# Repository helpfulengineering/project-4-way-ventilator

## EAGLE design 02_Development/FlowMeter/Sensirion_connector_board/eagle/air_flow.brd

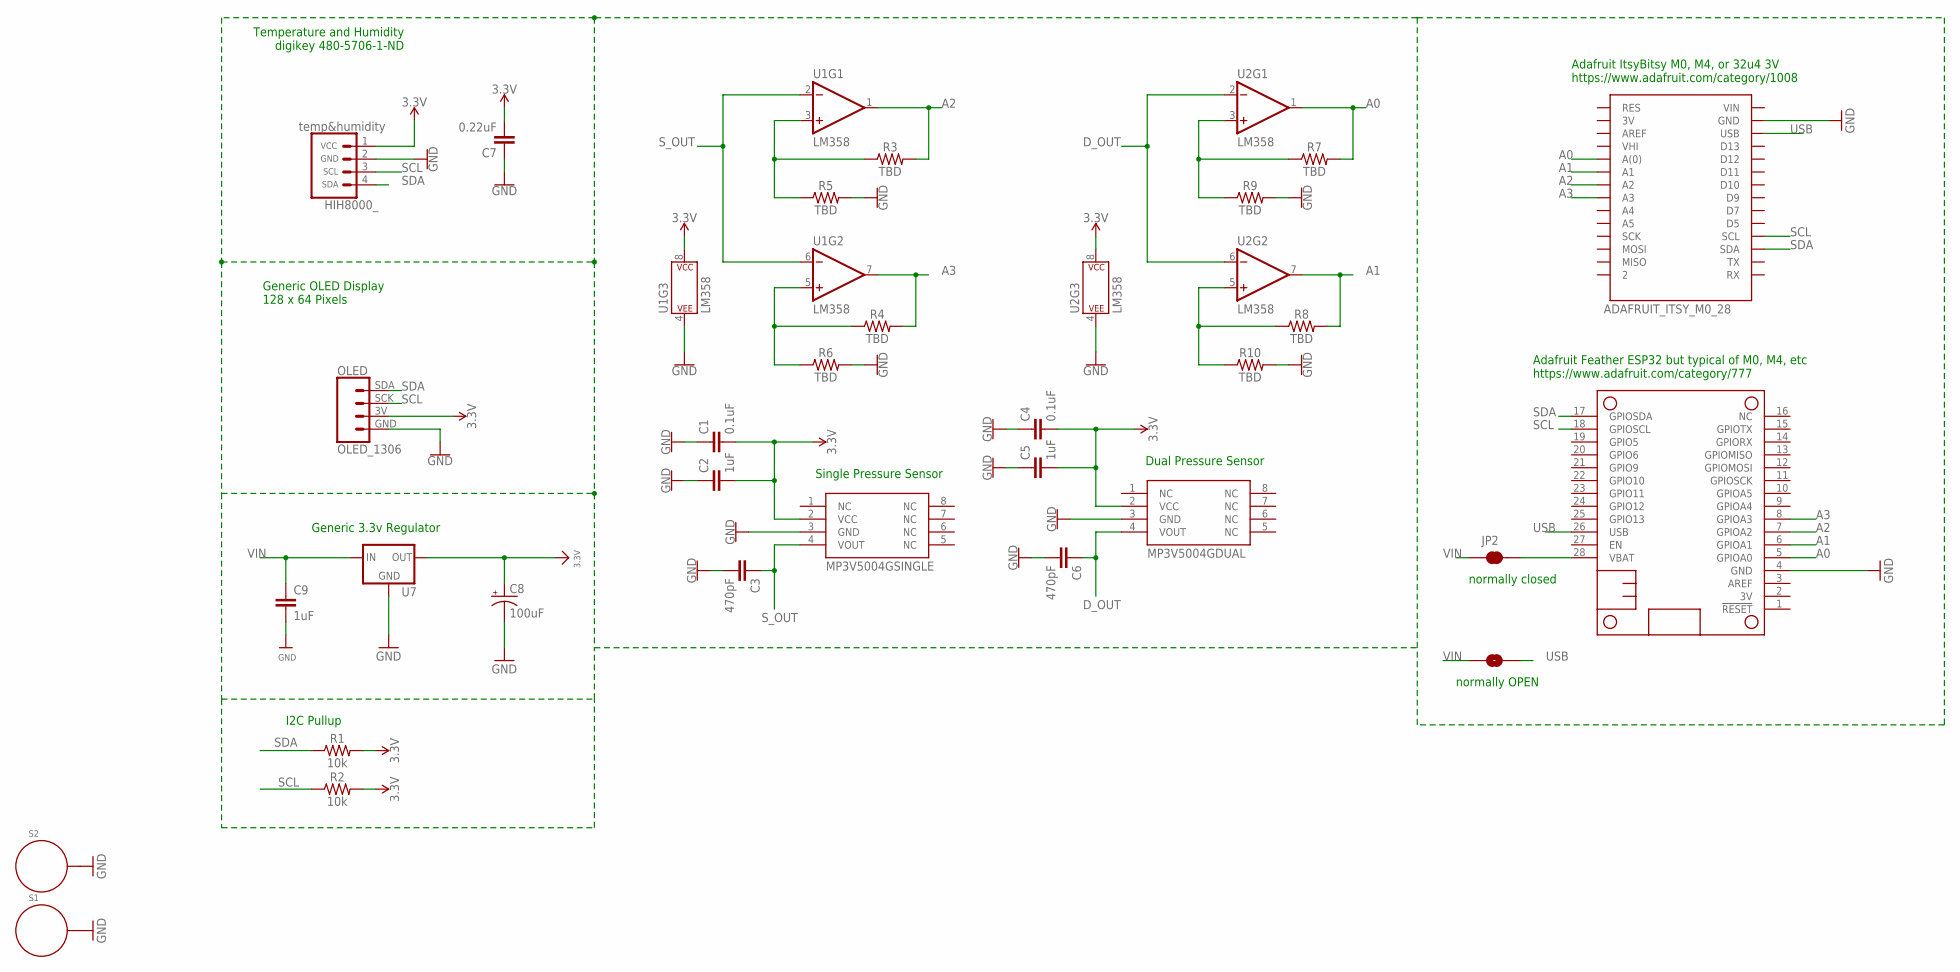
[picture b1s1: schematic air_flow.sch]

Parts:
C1, C4: 0.1uF; CAP-PTH-SMALL-KIT
C2, C5, C9: 1uF; CAP-PTH-SMALL-KIT
C3, C6: 470pF; CAP-PTH-SMALL-KIT
C7: 0.22uF; CAP-PTH-SMALL-KIT
C8: 100uF; E3,5-8
JP1: JUMPER-SMT_2_NO_NO-SILK; SMT-JUMPER_2_NO_NO-SILK
JP2: JUMPER-SMT_2_NC_TRACE_SILK; SMT-JUMPER_2_NC_TRACE_SILK
MS2: FEATHERWING_NODIM; FEATHERWING_DIM
R1, R2: 10k; AXIAL-0.3
R3, R4, R5, R6, R7, R8, R9, R10: TBD; AXIAL-0.3
S1, S2: STANDOFF_ELECTRICAL5-32; STANDOFF_ELECTRICAL_5_32
U1, U2: LM358; DIP08
U7: V_REG_78XXSINK; TO220-IGO
U$1: OLED_1306
U$2: MP3V5004GSINGLE; MP3V5004GP
U$3: MP3V5004GDUAL; MP3V5004DP
U$4: HIH8000_; HIH8120_TH
U$45: ADAFRUIT_ITSY_M0_28; ADAFRUIT_ITS_MO_28

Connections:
3.3V: C1.2, C2.2, C4.2, C5.2, C7.2, C8.+, R1.P$2 (2), R2.P$2 (2), U1.8 (P$V+), U2.8 (P$V+), U7.OUT, U$1.3V (VCC), U$2.2 (VCC), U$3.2 (VCC), U$4.1 (VCC)
A0: MS2.5 (GPIOA0), R7.P$2 (2), U2.1 (OUT), U$45.A0 (A(0))
A1: MS2.6 (GPIOA1), R8.P$2 (2), U2.7 (OUT), U$45.A1
A2: MS2.7 (GPIOA2), R3.P$2 (2), U1.1 (OUT), U$45.A2
A3: MS2.8 (GPIOA3), R4.P$2 (2), U1.7 (OUT), U$45.A3
D_OUT: C6.1, U2.2 (-IN), U2.6 (-IN), U$3.4 (VOUT)
GND: C1.1, C2.1, C3.2, C4.1, C5.1, C6.2, C7.1, C8.-, C9.2, MS2.4 (GND), R5.P$2 (2), R6.P$2 (2), R9.P$2 (2), R10.P$2 (2), S1.P1, S2.P1, U1.4 (P$V-), U2.4 (P$V-), U7.GND, U$1.GND, U$2.3 (GND), U$3.3 (GND), U$4.2 (GND), U$45.GND
unnamed: R3.P$1 (1), R5.P$1 (1), U1.3 (+IN)
unnamed: R4.P$1 (1), R6.P$1 (1), U1.5 (+IN)
unnamed: R7.P$1 (1), R9.P$1 (1), U2.3 (+IN)
unnamed: R8.P$1 (1), R10.P$1 (1), U2.5 (+IN)
SCL: MS2.18 (GPIOSCL), R2.P$1 (1), U$1.SCK, U$4.3 (SCL), U$45.SCL
SDA: MS2.17 (GPIOSDA), R1.P$1 (1), U$1.SDA, U$4.4 (SDA), U$45.SDA
S_OUT: C3.1, U1.2 (-IN), U1.6 (-IN), U$2.4 (VOUT)
USB: JP1.2, MS2.26 (USB), U$45.USB
VBAT: JP2.2, MS2.28 (VBAT)
VIN: C9.1, JP2.1, U7.IN

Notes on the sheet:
I2C Pullup
Dual Pressure Sensor
Single Pressure Sensor
Temperature and Humidity digikey 480-5706-1-ND
Generic OLED Display 128 x 64 Pixels
normally closed
normally OPEN
Adafruit ItsyBitsy M0, M4, or 32u4 3V https://www.adafruit.com/category/1008
Adafruit Feather ESP32 but typical of M0, M4, etc https://www.adafruit.com/category/777
Generic 3.3v Regulator

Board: 2 copper layers, 32 parts (1 on the bottom side), 17 nets, no tracks yet.

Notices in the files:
parts and their libraries:
SparkFun-Capacitors: Licensing: Creative Commons ShareAlike 4.0 International - https://creativecommons.org/licenses/by-sa/4.0
microbuilder: This work is placed in the public domain, and may be freely used for commercial and non-commercial work with the following conditions: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
